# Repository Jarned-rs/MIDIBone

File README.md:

# MIDIBone
a MIDI trombone using basic components to play every note possible! It uses an ESP32-S3-Zero by Waveshare with 4 keys and 7 MIDI keys.

# Features
- An ESP32-S3-Zero
- 7 MIDI note pads that are capacitive and
- 2 keys for octave up&down
- A key for Flats
- An OLED display to show the current note being played

# Hardware and Software
- An ESP32-S3-Zero
- 4 Cherry MX Switxhes
- 7 capacitive and are based on your touch
- A 0.96" OLED to show the note
- Python code to bind the notes to keys ect.

# Python
- code.py           | initializes the main controller
- config.py         | Stores pin assignments
- state.py          | Tracks the current note, flats and octave
- midi_out          | Sends the MIDI messages
- touch_scanner.py  | Reads inputs on the capacitive inputs
- display_ext.py    | Updates the OLED

# Schematic

# PCB

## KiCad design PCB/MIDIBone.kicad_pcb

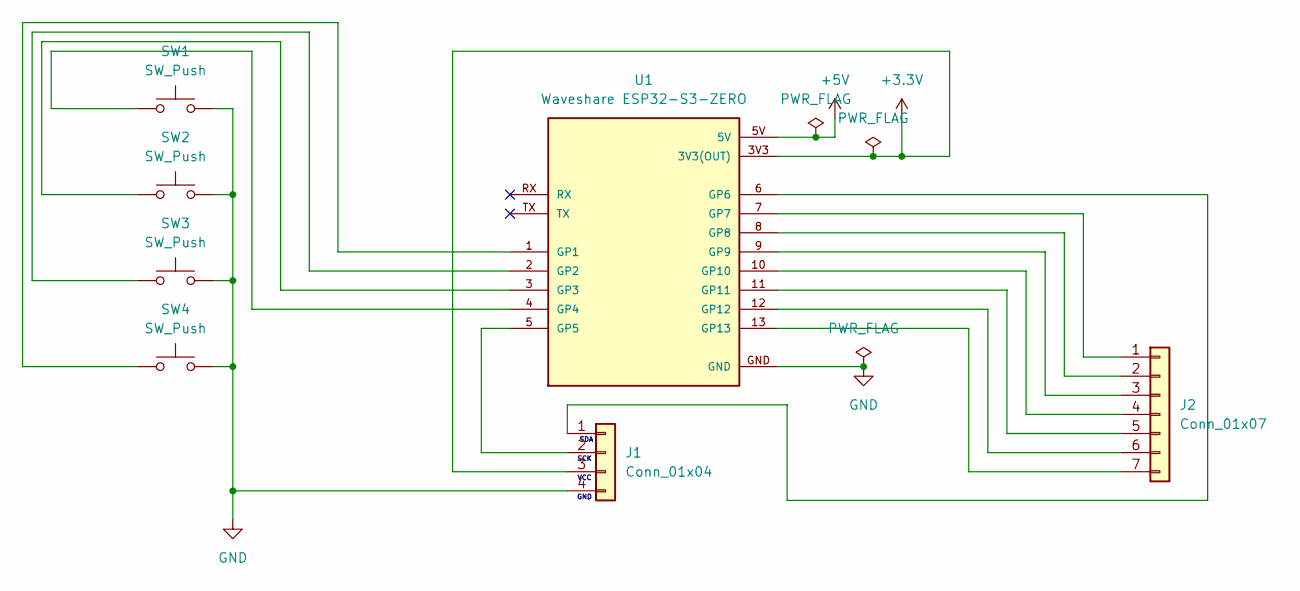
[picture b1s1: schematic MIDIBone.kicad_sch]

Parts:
J1: Conn_01x04; OLED_0.91_128x32
J2: Conn_01x07; MIDIBone_Keys_24x24
SW1, SW2, SW3, SW4: SW_Push; SW_Cherry_MX_1.00u_PCB
U1: Waveshare ESP32-S3-ZERO; Waveshare ESP32-S3-Zero; PARTREV NA

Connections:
+3.3V: J1.3, U1.3V3 (3V3(OUT))
+5V: U1.5V
GND: J1.4, SW1.2, SW2.2, SW3.2, SW4.2, U1.GND
unnamed: J1.1, U1.6 (GP6)
unnamed: J1.2, U1.5 (GP5)
unnamed: J2.1, U1.7 (GP7)
unnamed: J2.2, U1.8 (GP8)
unnamed: J2.3, U1.9 (GP9)
unnamed: J2.4, U1.10 (GP10)
unnamed: J2.5, U1.11 (GP11)
unnamed: J2.6, U1.12 (GP12)
unnamed: J2.7, U1.13 (GP13)
unnamed: SW4.1, U1.1 (GP1)
unnamed: SW3.1, U1.2 (GP2)
unnamed: SW2.1, U1.3 (GP3)
unnamed: SW1.1, U1.4 (GP4)

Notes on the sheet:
GND
SCK
SDA
VCC

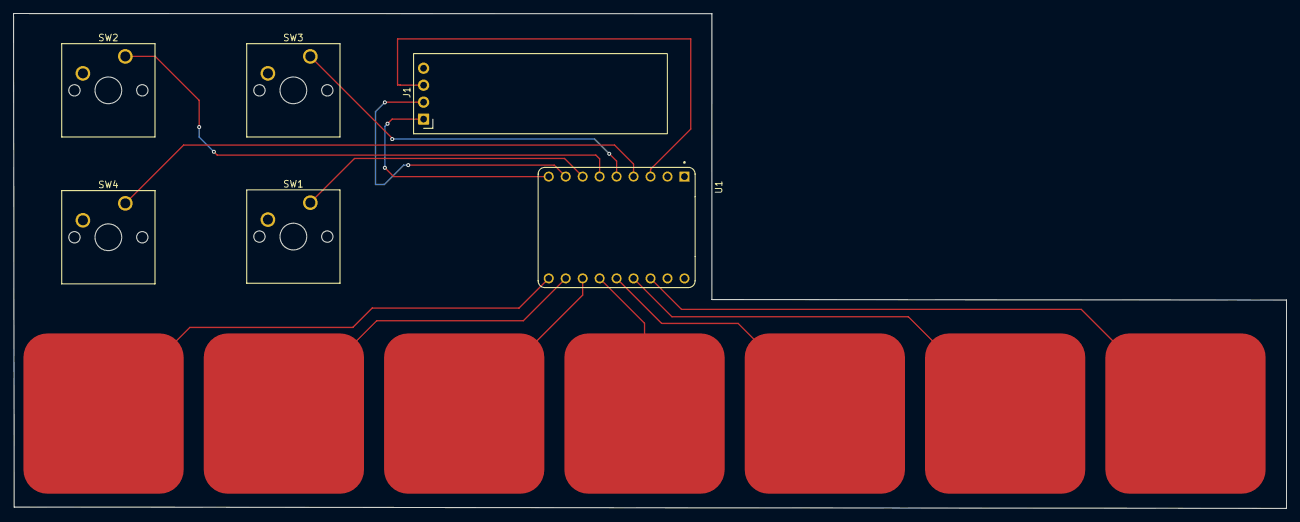
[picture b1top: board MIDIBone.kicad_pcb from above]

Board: 2 copper layers, 190.6 x 74.1 mm, 7 parts (0 on the bottom side), 15 nets.
